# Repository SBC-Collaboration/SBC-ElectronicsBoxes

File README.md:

This repository contains KiCAD drawings for the LED driver PCB design, LED driver box connections, and DIO box connections. It also has the SolidWorks drawings for the panel cutouts in those boxes for CNC machining.

## LED driver
This PCB design is for driving the LED rings at 100FPS with 1A current. Each board will be able to drive 20 IR LEDs (LZ1-00R402-0000) in series. The wiring into the PCB is connectorized, so if a board fails, it can be fixed by plugging into the backup board. The op-amp is also installed onto a DIP8 daughter board, so switching a burned-out op-amp does not require soldering in the box. 

## LED driver box
Three PCB boards drive one LED ring, consisted of 57 LEDs total (19 in each segment). There are three sets of boards in the box, corresponding to three LED rings, plus one backup board. Three 48V 3A power supplies each power one LED ring (three boards). Clock signals from the DIO box and the control voltage pins from the PLC go through DB15 and DB9 connectors, respectively. All digital grounds are connected together, but not necessarily shared with the chassis ground (because of the painted panels). Each LED segment is connected in series with a 1 Ohm power resistor that can be used to sense the current, and also protects the LEDs inside the chamber. On the back, each LED uses a 6-pin amphenol connector, one power and one return pins for each of the LED segments. 

## Digital I/O box
The DIO box is the central hub for all logic signals, including triggers, clocks, and camera controls. The back panel has four power supply jacks, each rated for 5V 3A. Three are passed through DB9s on the front panel to power the RPis for cameras, and one is used to power the USB hub. A USB jack on the back is connected to the hub, which in turn powers the three Arduinos and one NI USB device. One Arduino is responsible for trigger fan-in/fan-out. It takes trigger in and out from the 16 lemo connectors and the three camera DB9s on the front, as well as through the PLC DB9 on the back, and from the NI device from run control. The trigger reset signal comes from the NI device as well. THe clock Arduino sends clock out through the camera clock DB9 on the back, and also LED DB15 on the front. Another Ethernet jack is plugged into the ethernet shield on the Arduino for bellow position sensing. Two lemo connectors with isolated grounds are used for the sensing line for the position sensor, while the pulse signals are sent through the PLC DB9. Inside the box all digital grounds are connected together, and logic level converter or voltage divider is used for converting voltage between 3.3V(RPi), 5V (NI,Arduino,etc), and 24V (PLC).

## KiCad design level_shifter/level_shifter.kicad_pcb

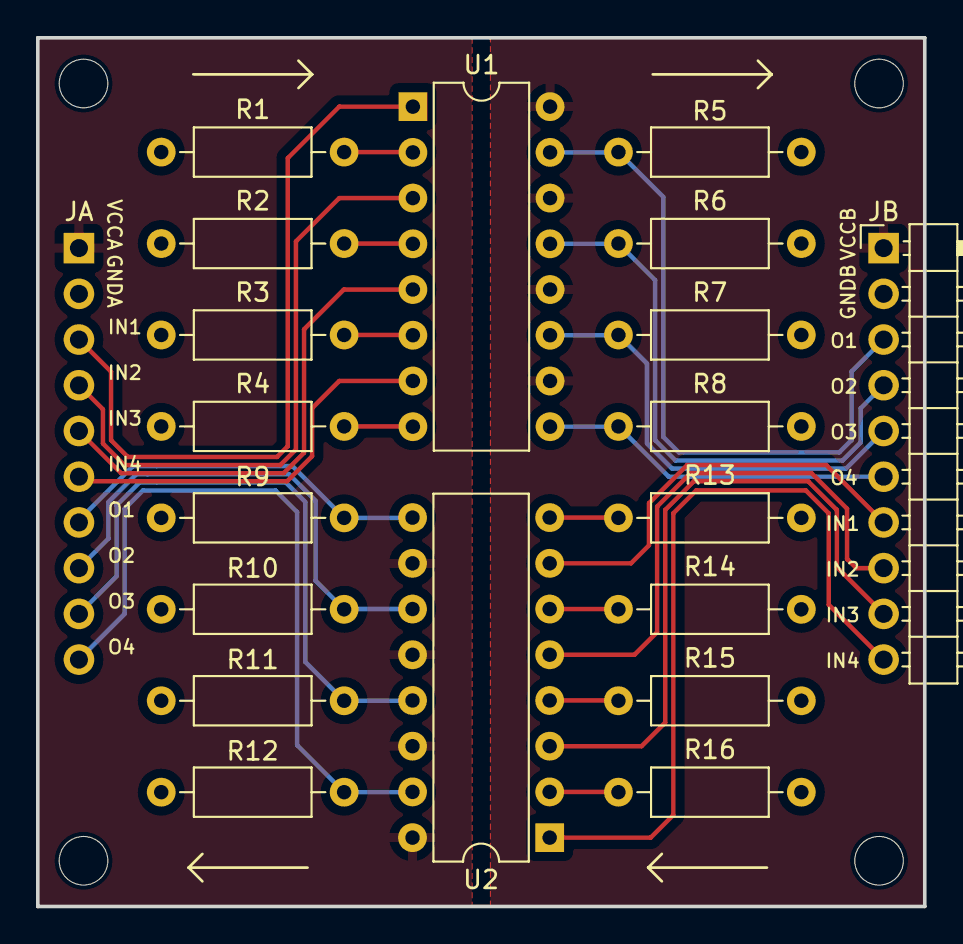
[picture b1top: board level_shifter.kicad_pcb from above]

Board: 2 copper layers, 49.3 x 48.3 mm, 20 parts (1 on the bottom side), 28 nets.

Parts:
JA: RPi connector; PinHeader_1x10_P2.54mm_Horizontal
JB: DIO connector; PinHeader_1x10_P2.54mm_Horizontal
R1, R2, R3, R4: 220R; R_Axial_DIN0207_L6.3mm_D2.5mm_P10.16mm_Horizontal
R5, R6, R7, R8: 1000R; R_Axial_DIN0207_L6.3mm_D2.5mm_P10.16mm_Horizontal
R9, R10, R11, R12: 620R; R_Axial_DIN0207_L6.3mm_D2.5mm_P10.16mm_Horizontal
R13, R14, R15, R16: 390R; R_Axial_DIN0207_L6.3mm_D2.5mm_P10.16mm_Horizontal
U1, U2: LTV-847; DIP-16_W7.62mm

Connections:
+3V3: JA.1, U2.10, U2.12, U2.14, U2.16
+5V: JB.1, U1.10, U1.12, U1.14, U1.16
GND: JB.2, R5.1, R6.2, R7.2, R8.2, R13.2, R14.2, R15.2, R16.2
GNDD: JA.2, R1.1, R2.1, R3.1, R4.1, R9.1, R10.1, R11.1, R12.1
unnamed: JA.3, U1.1
unnamed: JA.4, U1.3
unnamed: JA.5, U1.5
unnamed: JA.6, U1.7
unnamed: JA.7, R9.2, U2.9
unnamed: JA.8, R10.2, U2.11
unnamed: JA.9, R11.2, U2.13
unnamed: JA.10, R12.2, U2.15
unnamed: JB.3, R5.2, U1.15
unnamed: JB.4, R6.1, U1.13
unnamed: JB.5, R7.1, U1.11
unnamed: JB.6, R8.1, U1.9
unnamed: JB.7, U2.7
unnamed: JB.8, U2.5
unnamed: JB.9, U2.3
unnamed: JB.10, U2.1
unnamed: R1.2, U1.2
unnamed: R2.2, U1.4
unnamed: R3.2, U1.6
unnamed: R4.2, U1.8
unnamed: R13.1, U2.8
unnamed: R14.1, U2.6
unnamed: R15.1, U2.4
unnamed: R16.1, U2.2

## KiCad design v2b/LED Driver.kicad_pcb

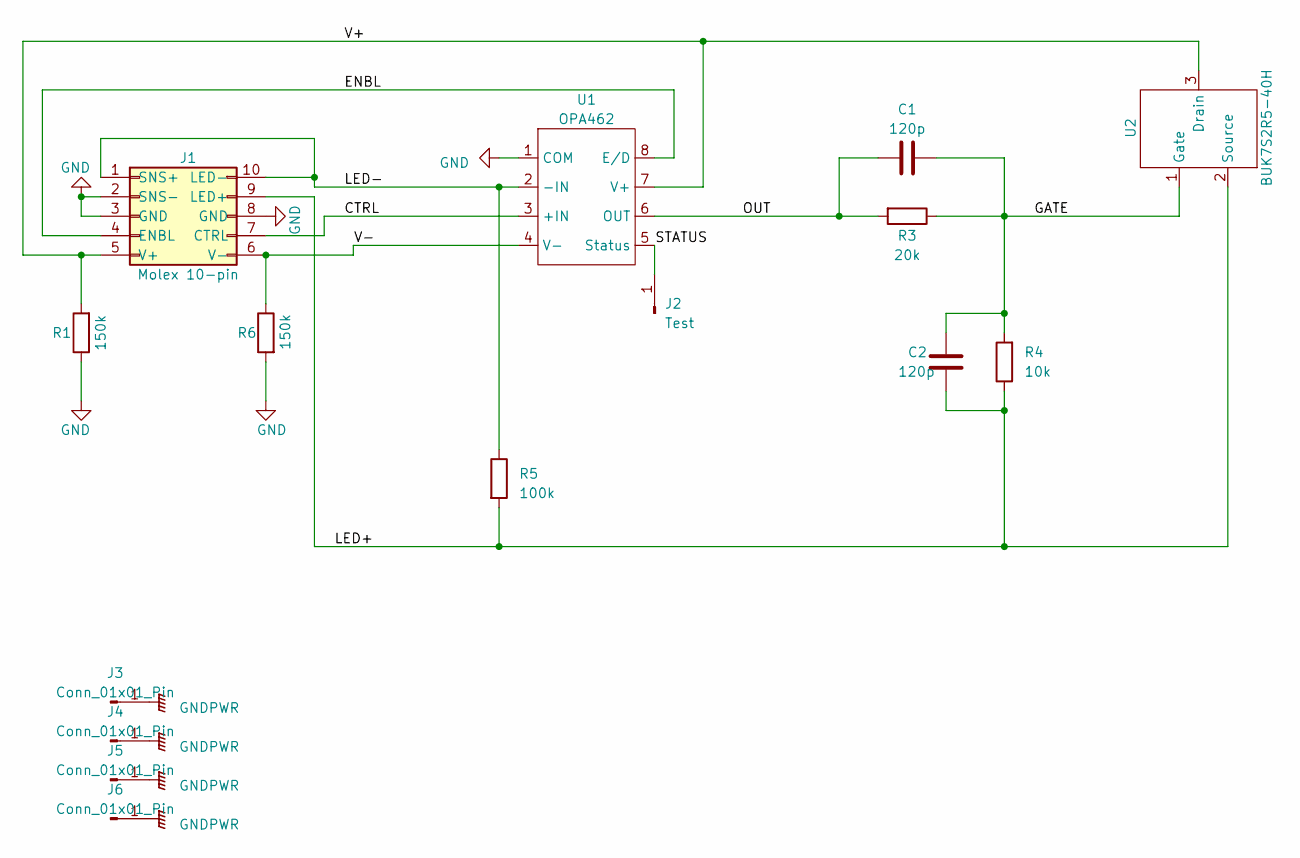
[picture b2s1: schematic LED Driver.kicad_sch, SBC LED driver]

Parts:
C1, C2: 120p; C_Disc_D7.0mm_W2.5mm_P5.00mm
J1: Molex 10-pin; molex_10pin
J2: Test; TestPoint_Pad_2.0x2.0mm
J3, J4, J5, J6: Conn_01x01_Pin; MountingHole_3.2mm_M3_DIN965_Pad
R1, R6: 150k; R_Axial_DIN0207_L6.3mm_D2.5mm_P10.16mm_Horizontal
R3: 20k; R_Axial_DIN0207_L6.3mm_D2.5mm_P10.16mm_Horizontal
R4: 10k; R_Axial_DIN0207_L6.3mm_D2.5mm_P10.16mm_Horizontal
R5: 100k; R_Axial_DIN0207_L6.3mm_D2.5mm_P10.16mm_Horizontal
U1: OPA462; DIP-8_W7.62mm
U2: BUK7S2R5-40H; BUK7S2R5-40H_footprint

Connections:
/CTRL: J1.7 (CTRL), U1.3 (+IN)
/ENBL: J1.4 (ENBL), U1.8 (E/D)
/GATE: C1.2, C2.2, R3.1, R4.2, U2.1 (Gate)
/LED+: C2.1, J1.9 (LED+), R4.1, R5.2, U2.2 (Source)
/LED-: J1.1 (SNS+), J1.10 (LED-), R5.1, U1.2 (-IN)
/OUT: C1.1, R3.2, U1.6 (OUT)
/STATUS: J2.1, U1.5 (Status)
/V+: J1.5 (V+), R1.2, U1.7 (V+), U2.3 (Drain)
/V-: J1.6 (V-), R6.1, U1.4 (V-)
GND: J1.2 (SNS-), J1.3 (GND), J1.8 (GND), R1.1, R6.2, U1.1 (COM)
GNDPWR: J3.1, J4.1, J5.1, J6.1

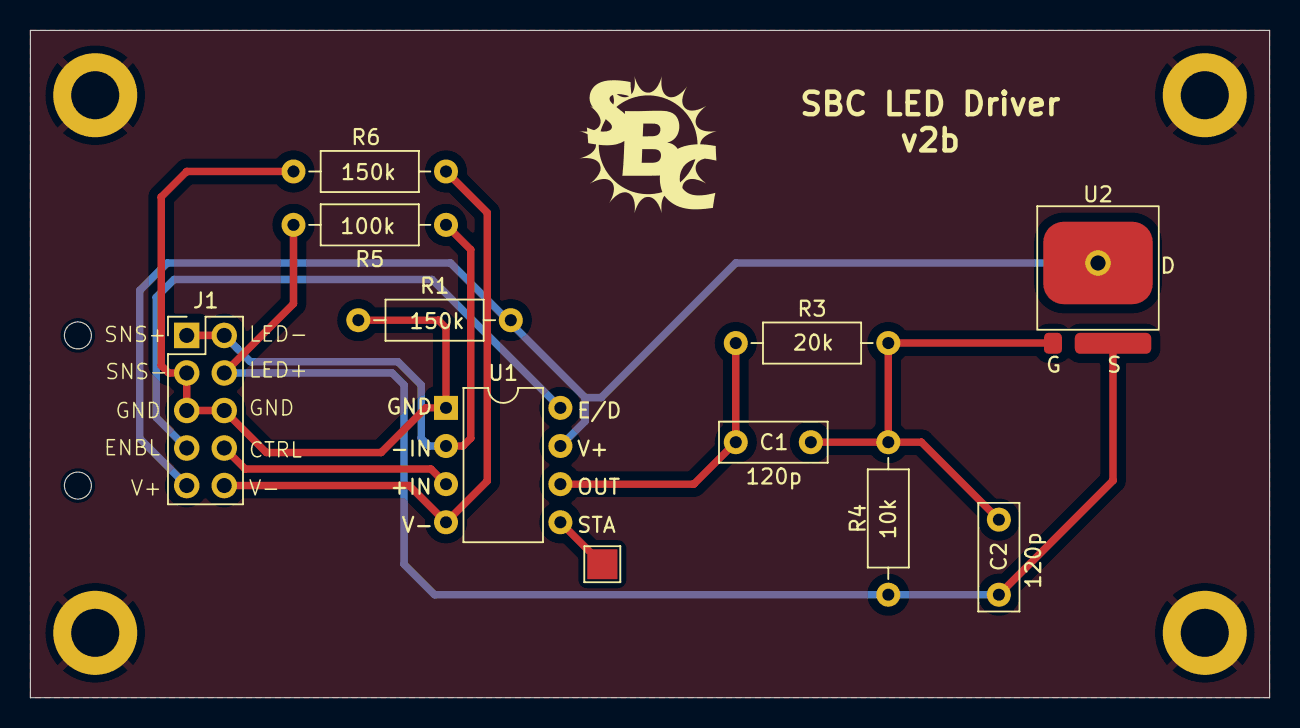
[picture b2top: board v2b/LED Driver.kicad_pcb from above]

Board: 2 copper layers, 82.5 x 44.4 mm, 15 parts (0 on the bottom side), 11 nets.

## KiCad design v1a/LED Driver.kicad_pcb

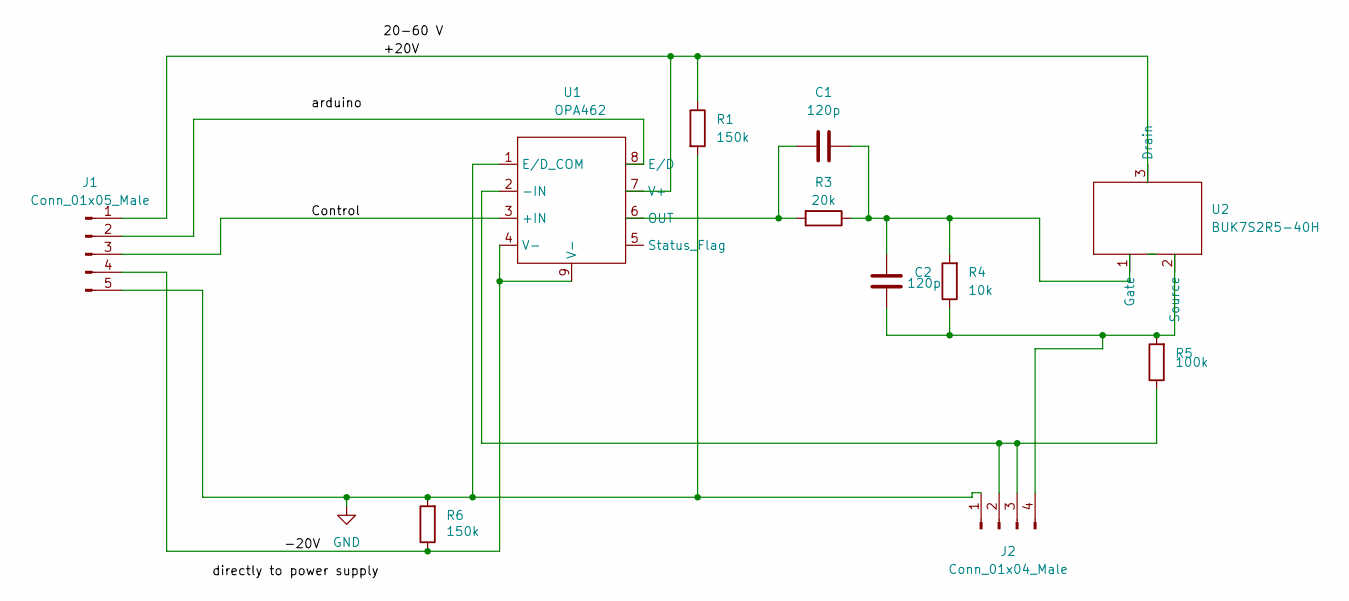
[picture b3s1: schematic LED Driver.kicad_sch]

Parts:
C1, C2: 120p; CP_Radial_D5.0mm_P2.50mm
J1: Conn_01x05_Male; PinHeader_1x05_P2.54mm_Vertical
J2: Conn_01x04_Male; PinHeader_1x04_P2.54mm_Vertical
R1, R6: 150k; R_Axial_DIN0207_L6.3mm_D2.5mm_P10.16mm_Horizontal
R3: 20k; R_Axial_DIN0207_L6.3mm_D2.5mm_P10.16mm_Horizontal
R4: 10k; R_Axial_DIN0207_L6.3mm_D2.5mm_P10.16mm_Horizontal
R5: 100k; R_Axial_DIN0207_L6.3mm_D2.5mm_P10.16mm_Horizontal
U1: OPA462; SOIC-8-1EP_3.9x4.9mm_P1.27mm_EP2.62x3.51mm_ThermalVias
U2: BUK7S2R5-40H; BUK7S2R5-40H_footprint

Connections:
/+20V: J1.1, R1.1, U1.7 (V+), U2.3 (Drain)
/-20V: J1.4, R6.1, U1.4 (V-), U1.9 (V-)
/Control: J1.3, U1.3 (+IN)
/arduino: J1.2, U1.8 (E/D)
GND: J1.5, J2.1, R1.2, R6.2, U1.1 (E/D_COM)
unnamed: C1.1, R3.2, U1.6 (OUT)
unnamed: C1.2, C2.2, R3.1, R4.2, U2.1 (Gate)
unnamed: C2.1, J2.4, R4.1, R5.2, U2.2 (Source)
unnamed: J2.2, J2.3, R5.1, U1.2 (-IN)

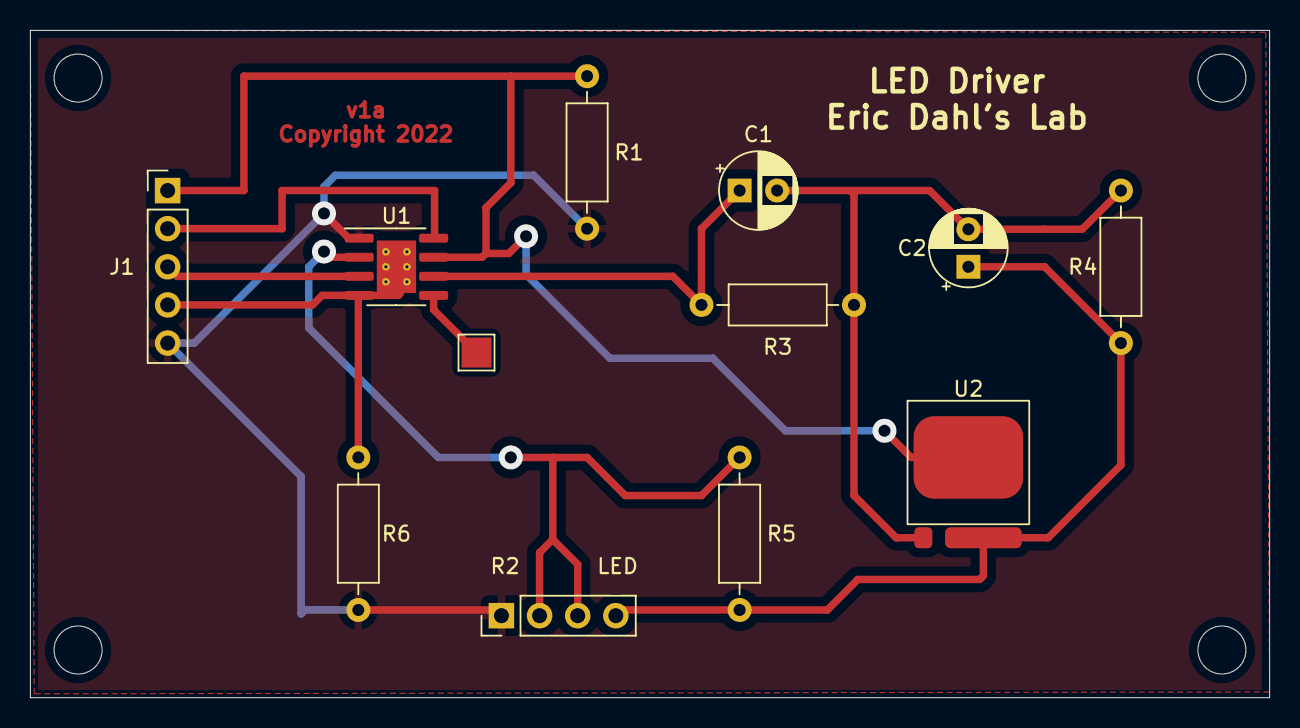
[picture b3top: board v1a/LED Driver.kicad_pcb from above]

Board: 2 copper layers, 82.5 x 44.5 mm, 11 parts (0 on the bottom side), 9 nets.

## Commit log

2023-05-23 Initial commit, completed v2a that has a molex connector and the opamp is installed onto a DIP8 carrier board. Started on schematic of driver box wiring and external wiring to the VJ
2023-05-23 Clean up folder structure, add page info
2023-05-26 Modified led driver box wiring
2023-05-30 Update to the LED driver box wiring schematic
2023-05-30 Modified to v2b version, where the copper layer on PCB is connected to chassis and mounting holes, which is separated from all electric grounds (arduino, power supply, PLC, etc)
2023-05-31 Change LED terminal blocks to include fuse
2023-05-31 Fix a disconnected SNS+ pin, generate new output files
2023-07-19 Update sense resistor wiring for LED driver box, also aupdated PCB schematic to reflect the added resistor between out and V- on opamp
2023-09-25 Working on digital IO box schematic drawing. Creating one sheet for internal connections between the arduinos and NI USB device
2023-09-26 Finishing up all connections. Added DB9 for camera FSYN, and lemo for clock to CAEN
2023-09-28 Added trigger first fault pins from FIFO arduino, and the LED/camera clock enable pins from clock arduino.
2023-09-28 Added arrows to indicate input/output for relevant pins.
2023-10-02 Added solidworks drawing for connector cutouts for CNC
2023-10-02 Added some drawings for DIO box cutouts
2023-10-03 Added drawings for USB and ethernet cutouts
2023-10-04 Generate .PRT files from .ASM files. Then generate DXF files for CNC machining
2023-10-05 Added readme documentation
2023-10-06 Change orientation of drawing
2024-01-10 Schematic drawings for the piezo amplifying box, without detailed drawing of the amp PCB
2024-03-06 Updated LED driver MOSFET part number, updated DIO box wirings as it's being made
2024-03-09 Modified DIO wiring, changed some NI USB and trigger pinouts
2024-03-09 Clean up archive files
2024-05-20 Start schematic drawing for level shifter using optocoupler
2024-05-20 Replace design to use 847 instead of 817 so 4 channels per chip. Also removed the inverting logic version
2024-05-21 Change circuit so that while still non-inverting logic, the LED in optocoupler will only turn on when input is high
2024-05-21 Draw up first version of PCB board
2024-05-21 minor changes, change mounting hole
2024-05-21 minor changes
2024-06-03 Add 5V to 24V resistor values in another drawing
2024-06-20 Start drawing the pizeo fuse box
2024-06-21 Add ch8 connectors, and fix pin directions
2024-06-21 Add DIO and acoustics boxes for the wiring plot
2024-06-21 Draw gage and caen digitizers, switch, run control. Moved VJ feedthroughs to its own sheet
2024-06-21 Testing symlinks
2024-07-01 Cleaning up some old drawings
2024-07-10 Change level shifter resistance values
2024-07-10 24v to 5v level shifter
2024-09-18 Add fire alarm and power connections in instrumentation wiring
2024-09-23 upload coupp piezo amp board drawing
2024-12-11 Version 1 of ORC schematic documents
2025-01-08 Change pin for fast compress trigger to PLC, also update to newer version of kicad

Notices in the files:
v1a/LED Driver.kicad_pcb:
Copyright 2022
